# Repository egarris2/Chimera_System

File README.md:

View this project on [CADLAB.io](https://cadlab.io/project/27528). 

# Chimera_System
A modular PCB system designed for rapid iteration and extreme flexibility in application.

All PCBs are designed in KiCAD 7. They utilize components that are available from the easyEDA component library which allows for quick generation of manufacturing files for order of assembly from JLCPCB.

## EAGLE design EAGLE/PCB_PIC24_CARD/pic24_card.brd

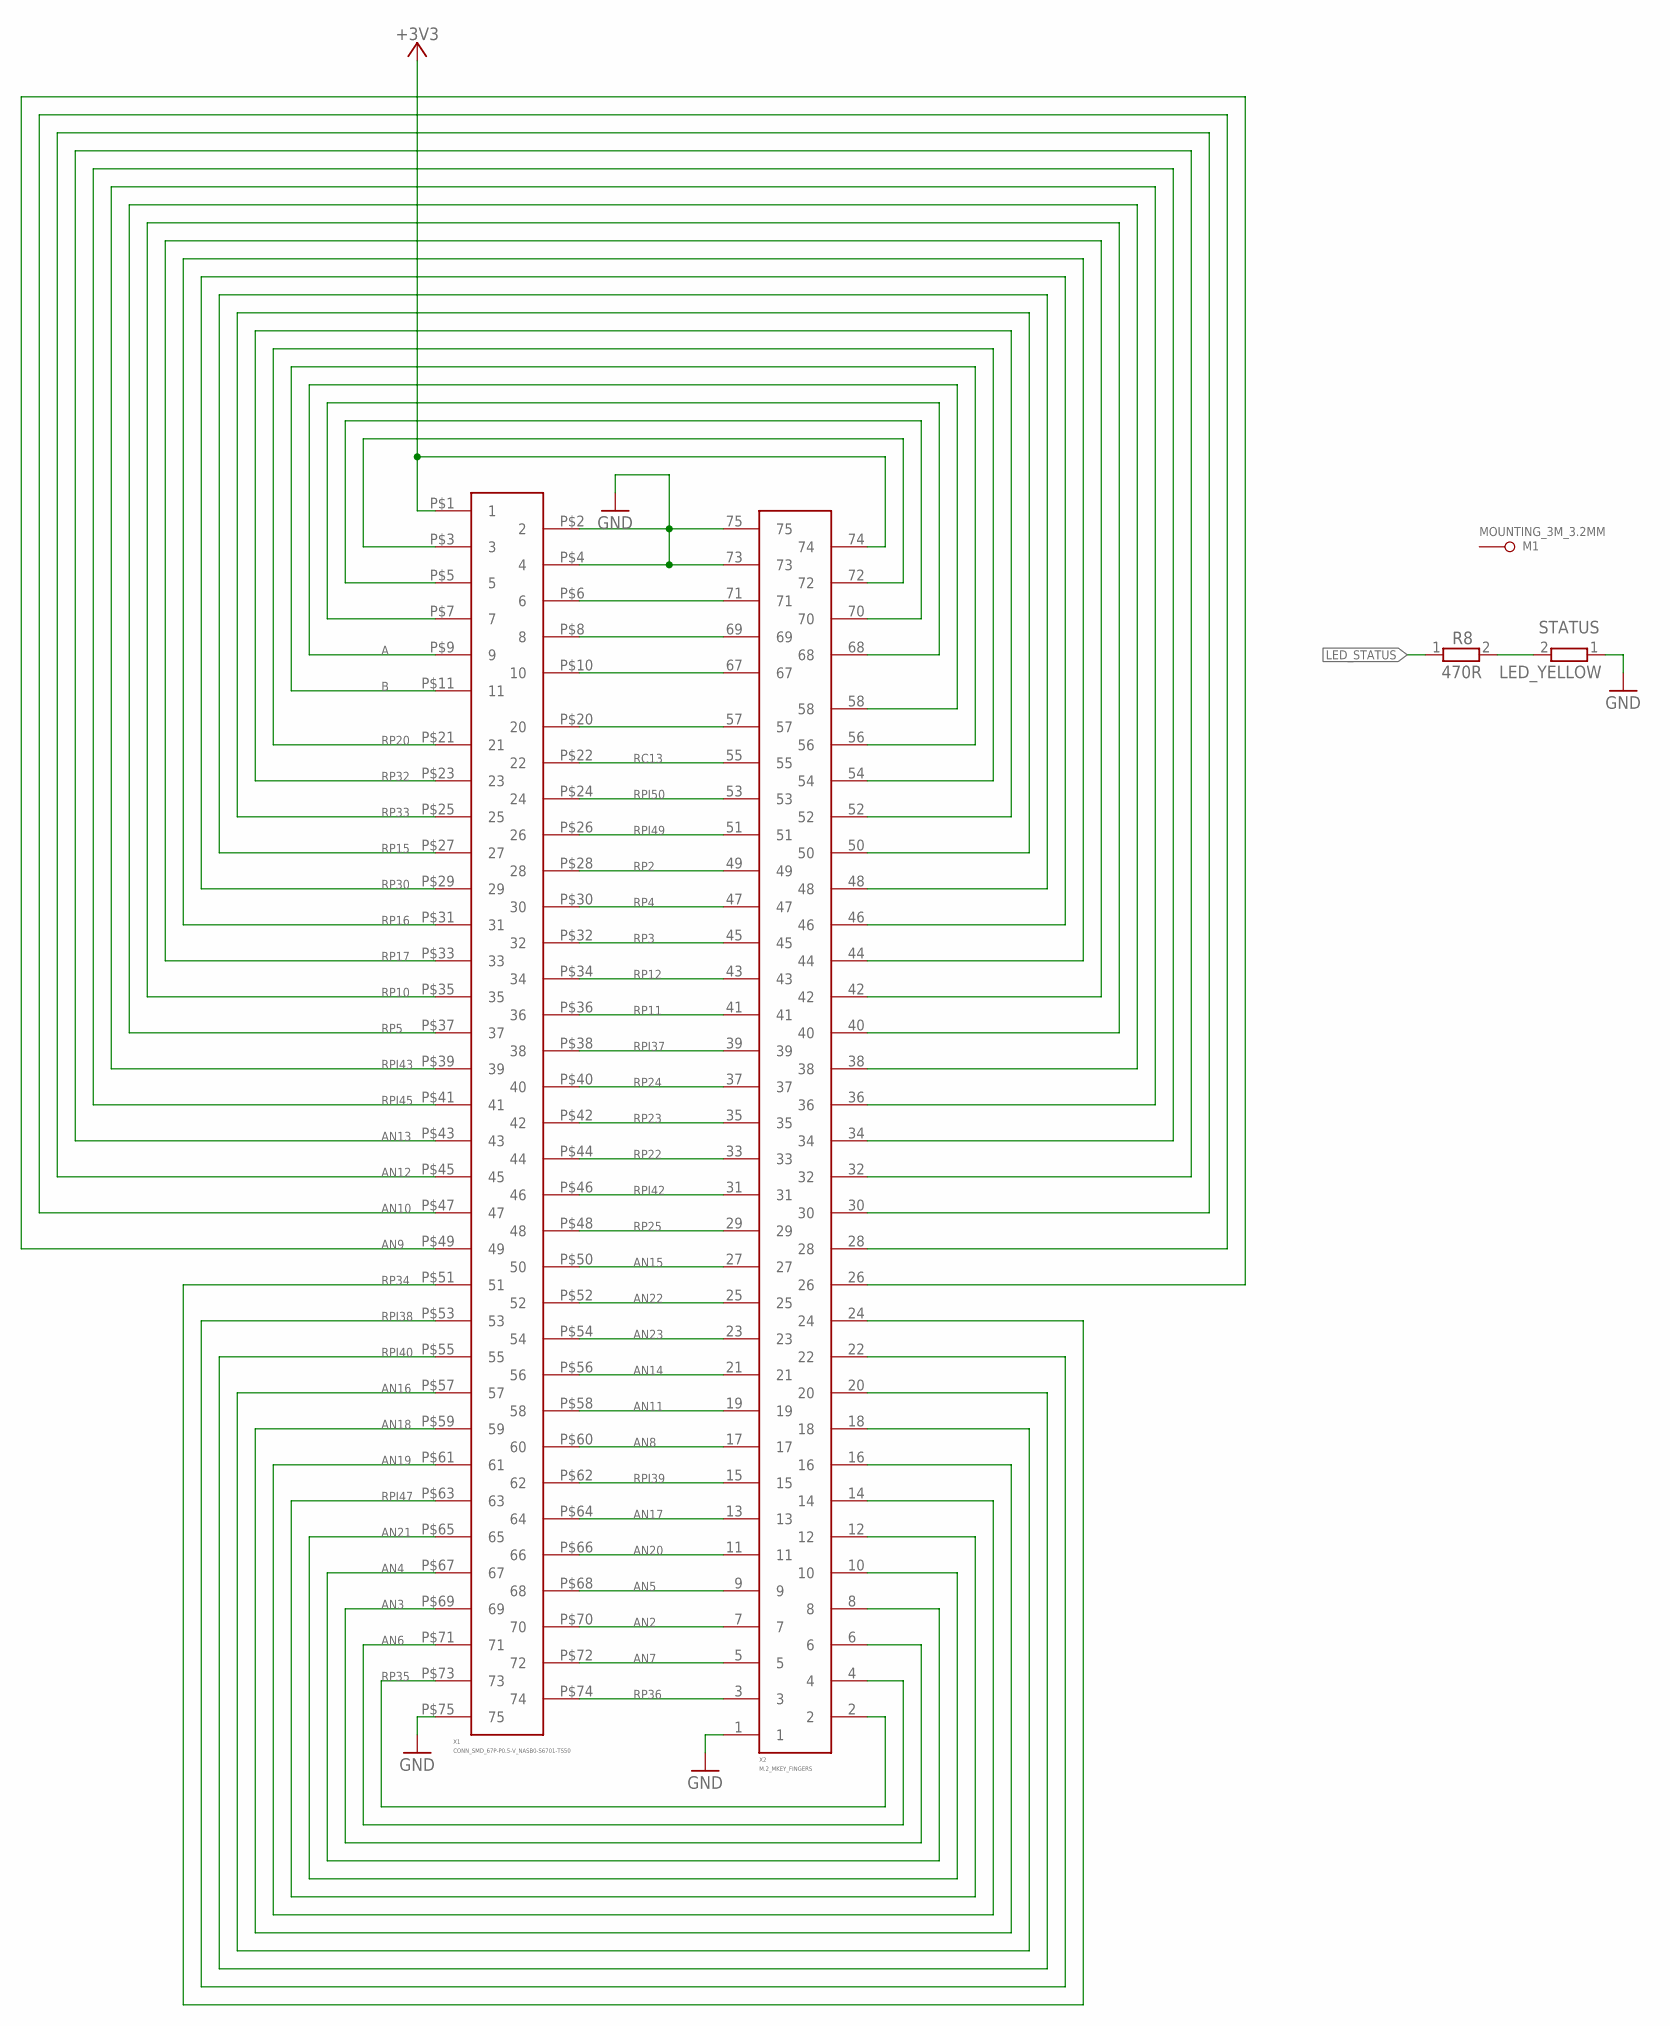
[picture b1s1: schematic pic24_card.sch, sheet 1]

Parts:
M1: MOUNTING_3M_3.2MM
R8: 470R; R0402_NIBE
STATUS: LED_YELLOW; R0603
X1: CONN_SMD_67P-P0.5-V_NASB0-S6701-TS50
X2: M.2_MKEY_FINGERS

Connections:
+3V3: X1.P$1 (1), X2.74; also elsewhere on the board
A: X1.P$9 (9), X2.58; also elsewhere on the board
AN2: X1.P$70 (70), X2.7; also elsewhere on the board
AN3: X1.P$69 (69), X2.6; also elsewhere on the board
AN4: X1.P$67 (67), X2.8; also elsewhere on the board
AN5: X1.P$68 (68), X2.9; also elsewhere on the board
AN6: X1.P$71 (71), X2.4; also elsewhere on the board
AN7: X1.P$72 (72), X2.5; also elsewhere on the board
AN8: X1.P$60 (60), X2.17; also elsewhere on the board
AN9: X1.P$49 (49), X2.26; also elsewhere on the board
AN10: X1.P$47 (47), X2.28; also elsewhere on the board
AN11: X1.P$58 (58), X2.19; also elsewhere on the board
AN12: X1.P$45 (45), X2.30; also elsewhere on the board
AN13: X1.P$43 (43), X2.32; also elsewhere on the board
AN14: X1.P$56 (56), X2.21; also elsewhere on the board
AN15: X1.P$50 (50), X2.27; also elsewhere on the board
AN16: X1.P$57 (57), X2.18; also elsewhere on the board
AN17: X1.P$64 (64), X2.13; also elsewhere on the board
AN18: X1.P$59 (59), X2.16; also elsewhere on the board
AN19: X1.P$61 (61), X2.14; also elsewhere on the board
AN20: X1.P$66 (66), X2.11; also elsewhere on the board
AN21: X1.P$65 (65), X2.10; also elsewhere on the board
AN22: X1.P$52 (52), X2.25; also elsewhere on the board
AN23: X1.P$54 (54), X2.23; also elsewhere on the board
B: X1.P$11 (11), X2.56; also elsewhere on the board
GND: STATUS.1 (2), X1.P$2 (2), X1.P$4 (4), X1.P$75 (75), X2.1, X2.73, X2.75; also elsewhere on the board
LED_STATUS: R8.1; also elsewhere on the board
unnamed: R8.2, STATUS.2 (1)
unnamed: X1.P$7 (7), X2.68
unnamed: X1.P$5 (5), X2.70
unnamed: X1.P$3 (3), X2.72
unnamed: X1.P$6 (6), X2.71
unnamed: X1.P$8 (8), X2.69
unnamed: X1.P$10 (10), X2.67
unnamed: X1.P$20 (20), X2.57
RC13: X1.P$22 (22), X2.55; also elsewhere on the board
RP2: X1.P$28 (28), X2.49; also elsewhere on the board
RP3: X1.P$32 (32), X2.45; also elsewhere on the board
RP4: X1.P$30 (30), X2.47; also elsewhere on the board
RP5: X1.P$37 (37), X2.38; also elsewhere on the board
RP10: X1.P$35 (35), X2.40; also elsewhere on the board
RP11: X1.P$36 (36), X2.41; also elsewhere on the board
RP12: X1.P$34 (34), X2.43; also elsewhere on the board
RP15: X1.P$27 (27), X2.48; also elsewhere on the board
RP16: X1.P$31 (31), X2.44; also elsewhere on the board
RP17: X1.P$33 (33), X2.42; also elsewhere on the board
RP20: X1.P$21 (21), X2.54; also elsewhere on the board
RP22: X1.P$44 (44), X2.33; also elsewhere on the board
RP23: X1.P$42 (42), X2.35; also elsewhere on the board
RP24: X1.P$40 (40), X2.37; also elsewhere on the board
RP25: X1.P$48 (48), X2.29; also elsewhere on the board
RP30: X1.P$29 (29), X2.46; also elsewhere on the board
RP32: X1.P$23 (23), X2.52; also elsewhere on the board
RP33: X1.P$25 (25), X2.50; also elsewhere on the board
RP34: X1.P$51 (51), X2.24; also elsewhere on the board
RP35: X1.P$73 (73), X2.2; also elsewhere on the board
RP36: X1.P$74 (74), X2.3; also elsewhere on the board
RPI37: X1.P$38 (38), X2.39; also elsewhere on the board
RPI38: X1.P$53 (53), X2.22; also elsewhere on the board
RPI39: X1.P$62 (62), X2.15; also elsewhere on the board
RPI40: X1.P$55 (55), X2.20; also elsewhere on the board
RPI42: X1.P$46 (46), X2.31; also elsewhere on the board
RPI43: X1.P$39 (39), X2.36; also elsewhere on the board
RPI45: X1.P$41 (41), X2.34; also elsewhere on the board
RPI47: X1.P$63 (63), X2.12; also elsewhere on the board
RPI49: X1.P$26 (26), X2.51; also elsewhere on the board
RPI50: X1.P$24 (24), X2.53; also elsewhere on the board

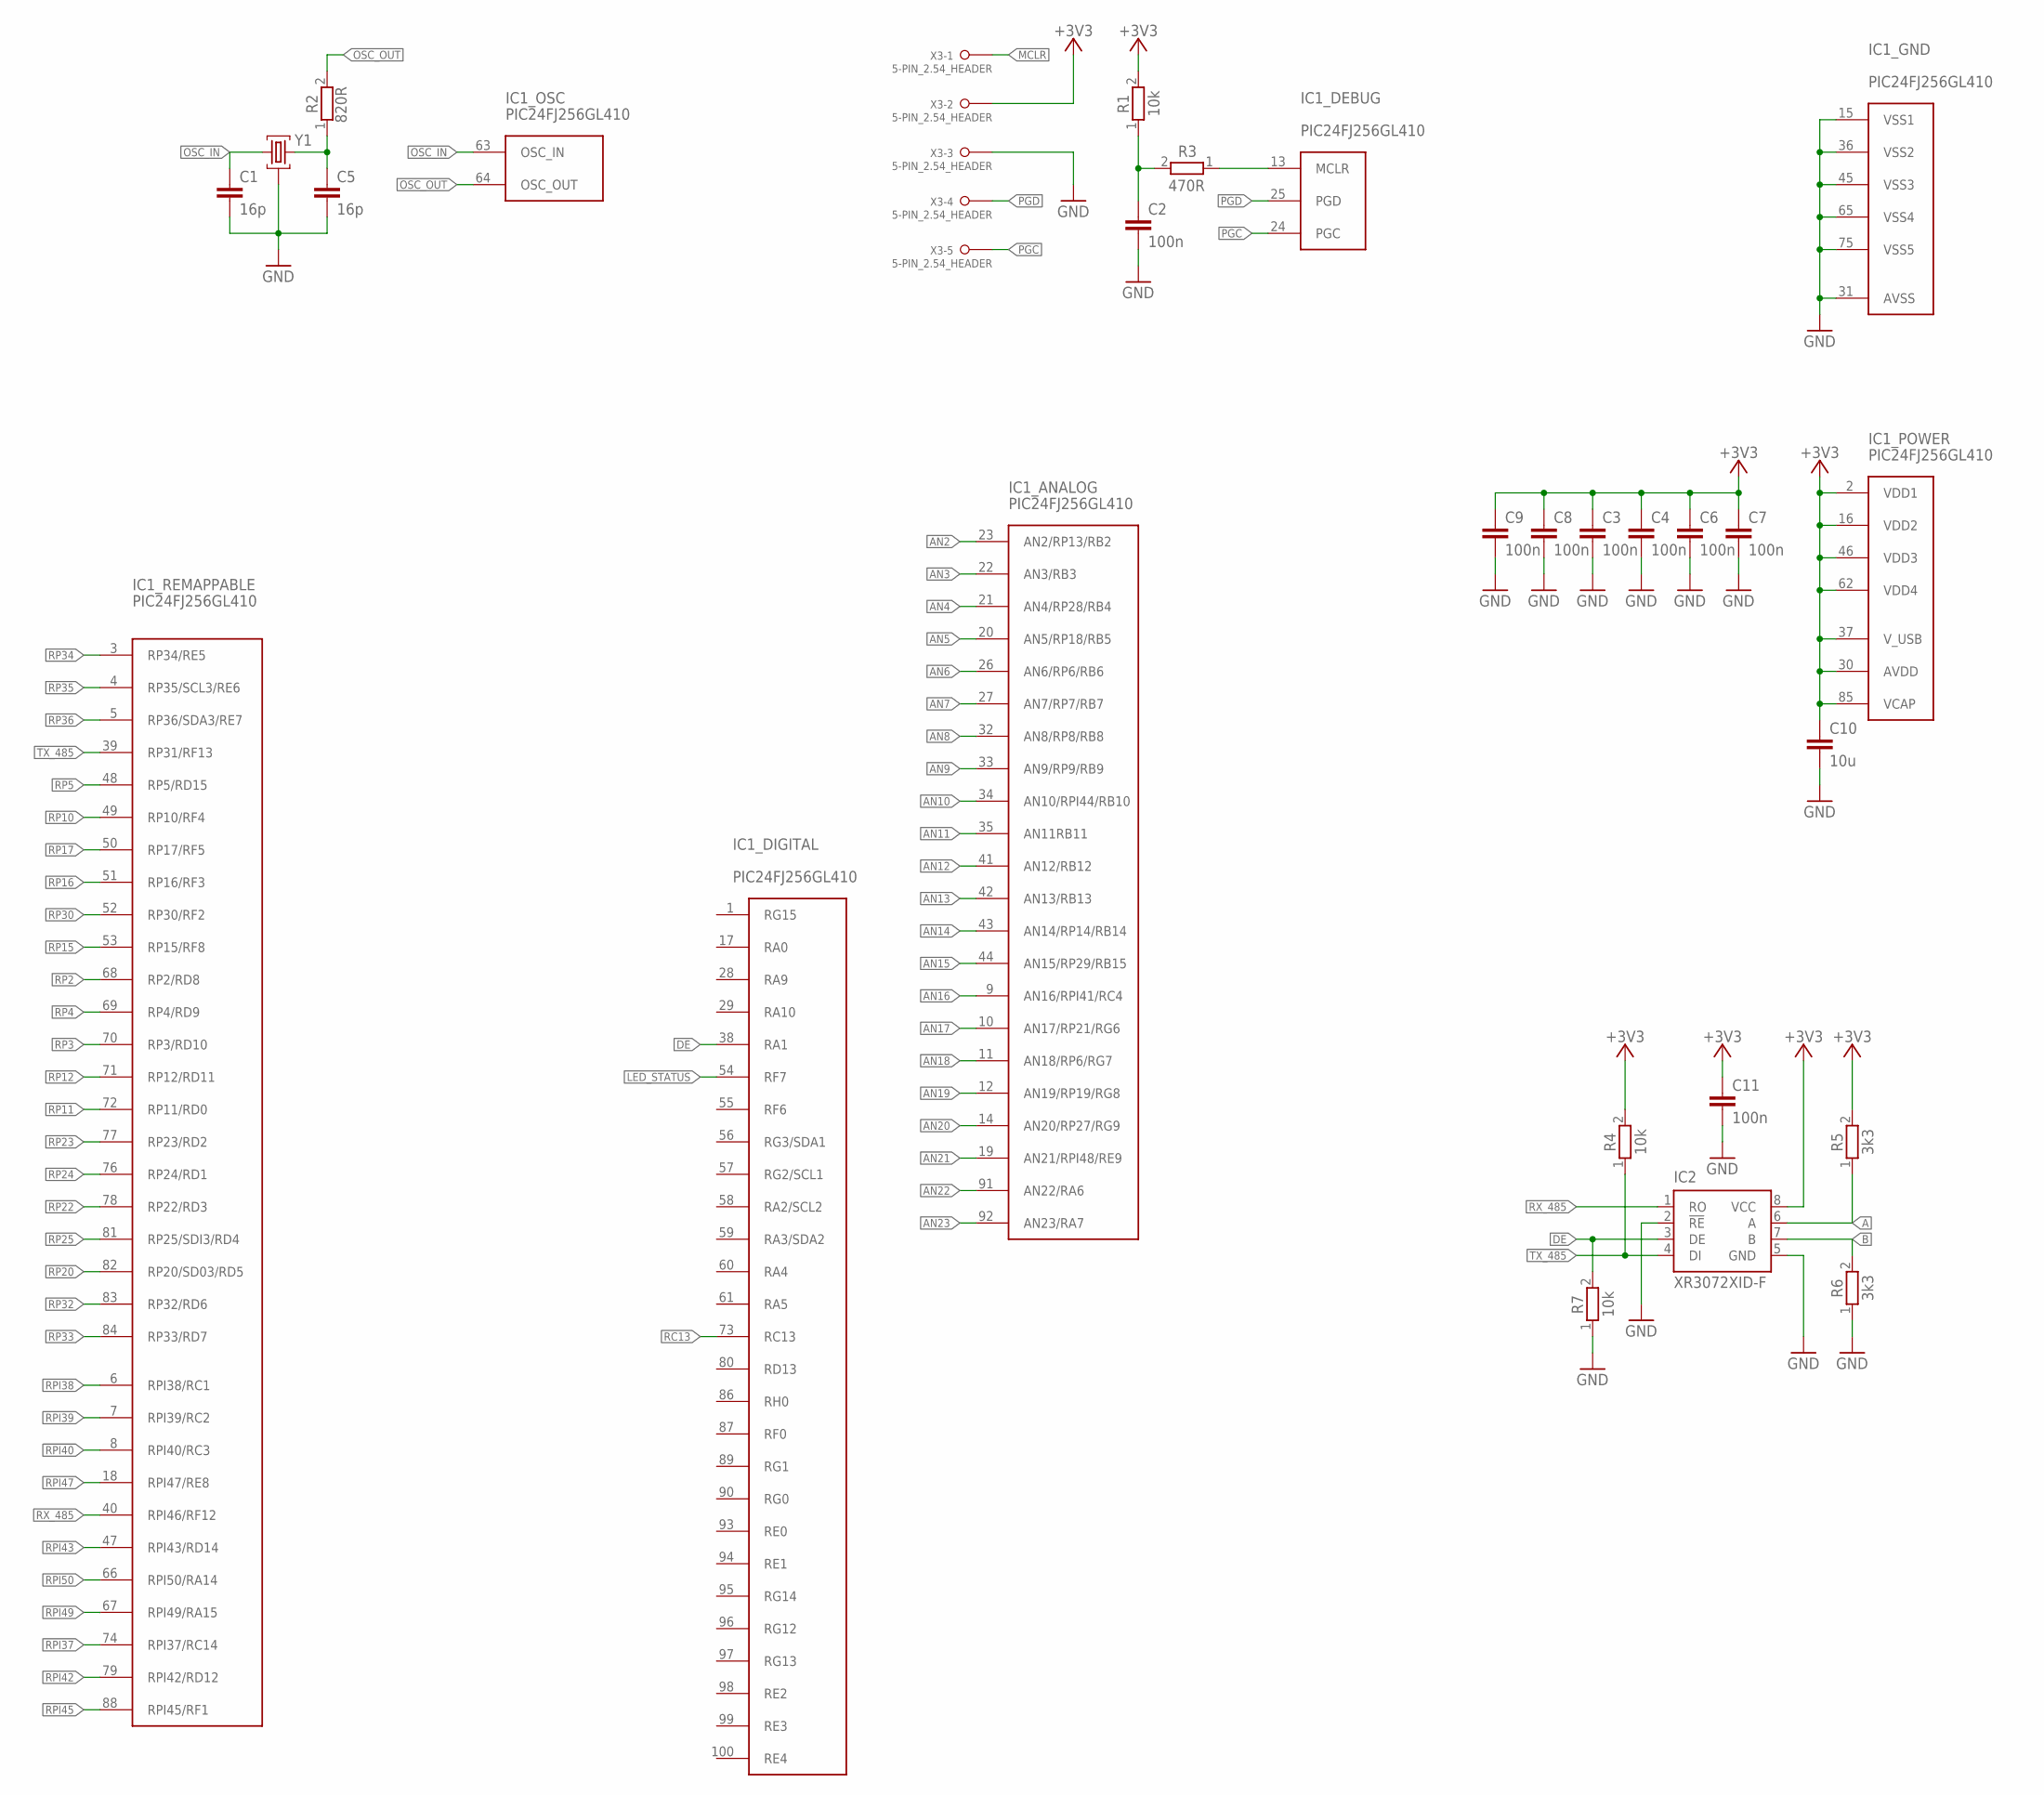
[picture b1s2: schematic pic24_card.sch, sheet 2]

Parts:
C1, C5: 16p; C0402_NIBE
C2, C3, C4, C6, C7, C8, C9, C11: 100n; C0402_NIBE
C10: 10u; C0805
IC1: PIC24FJ256GL410
IC2: XR3072XID-F; SOIC8
R1, R4, R7: 10k; R0402_NIBE
R2: 820R; R0402_NIBE
R3: 470R; R0402_NIBE
R5, R6: 3k3; R0402_NIBE
X3: 5-PIN_2.54_HEADER; 2.54MM_5HOLE_TH
Y1: FA238-12MHZ; FA238

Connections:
+3V3: C3.1, C4.1, C6.1, C7.1, C8.1, C9.1, C10.1, C11.1, IC1.2 (VDD1), IC1.16 (VDD2), IC1.30 (AVDD), IC1.37 (V_USB), IC1.46 (VDD3), IC1.62 (VDD4), IC1.85 (VCAP), IC2.8 (VCC), R1.2, R4.2, R5.2, X3.2; also elsewhere on the board
A: IC2.6 (A), R5.1; also elsewhere on the board
AN2: IC1.23 (AN2/RP13/RB2); also elsewhere on the board
AN3: IC1.22 (AN3/RB3); also elsewhere on the board
AN4: IC1.21 (AN4/RP28/RB4); also elsewhere on the board
AN5: IC1.20 (AN5/RP18/RB5); also elsewhere on the board
AN6: IC1.26 (AN6/RP6/RB6); also elsewhere on the board
AN7: IC1.27 (AN7/RP7/RB7); also elsewhere on the board
AN8: IC1.32 (AN8/RP8/RB8); also elsewhere on the board
AN9: IC1.33 (AN9/RP9/RB9); also elsewhere on the board
AN10: IC1.34 (AN10/RPI44/RB10); also elsewhere on the board
AN11: IC1.35 (AN11RB11); also elsewhere on the board
AN12: IC1.41 (AN12/RB12); also elsewhere on the board
AN13: IC1.42 (AN13/RB13); also elsewhere on the board
AN14: IC1.43 (AN14/RP14/RB14); also elsewhere on the board
AN15: IC1.44 (AN15/RP29/RB15); also elsewhere on the board
AN16: IC1.9 (AN16/RPI41/RC4); also elsewhere on the board
AN17: IC1.10 (AN17/RP21/RG6); also elsewhere on the board
AN18: IC1.11 (AN18/RP6/RG7); also elsewhere on the board
AN19: IC1.12 (AN19/RP19/RG8); also elsewhere on the board
AN20: IC1.14 (AN20/RP27/RG9); also elsewhere on the board
AN21: IC1.19 (AN21/RPI48/RE9); also elsewhere on the board
AN22: IC1.91 (AN22/RA6); also elsewhere on the board
AN23: IC1.92 (AN23/RA7); also elsewhere on the board
B: IC2.7 (B), R6.2; also elsewhere on the board
DE: IC1.38 (RA1), IC2.3 (DE), R7.2
GND: C1.2, C2.2, C3.2, C4.2, C5.2, C6.2, C7.2, C8.2, C9.2, C10.2, C11.2, IC1.15 (VSS1), IC1.31 (AVSS), IC1.36 (VSS2), IC1.45 (VSS3), IC1.65 (VSS4), IC1.75 (VSS5), IC2.2 (!RE), IC2.5 (GND), R6.1, R7.1, X3.3, Y1.2, Y1.4 (2); also elsewhere on the board
LED_STATUS: IC1.54 (RF7); also elsewhere on the board
MCLR: IC1.13 (MCLR), R3.1, X3.1
unnamed: C2.1, R1.1, R3.2
unnamed: C5.1, R2.1, Y1.3
OSC_IN: C1.1, IC1.63 (OSC_IN), Y1.1
OSC_OUT: IC1.64 (OSC_OUT), R2.2
PGC: IC1.24 (PGC), X3.5
PGD: IC1.25 (PGD), X3.4
RC13: IC1.73 (RC13); also elsewhere on the board
RP2: IC1.68 (RP2/RD8); also elsewhere on the board
RP3: IC1.70 (RP3/RD10); also elsewhere on the board
RP4: IC1.69 (RP4/RD9); also elsewhere on the board
RP5: IC1.48 (RP5/RD15); also elsewhere on the board
RP10: IC1.49 (RP10/RF4); also elsewhere on the board
RP11: IC1.72 (RP11/RD0); also elsewhere on the board
RP12: IC1.71 (RP12/RD11); also elsewhere on the board
RP15: IC1.53 (RP15/RF8); also elsewhere on the board
RP16: IC1.51 (RP16/RF3); also elsewhere on the board
RP17: IC1.50 (RP17/RF5); also elsewhere on the board
RP20: IC1.82 (RP20/SD03/RD5); also elsewhere on the board
RP22: IC1.78 (RP22/RD3); also elsewhere on the board
RP23: IC1.77 (RP23/RD2); also elsewhere on the board
RP24: IC1.76 (RP24/RD1); also elsewhere on the board
RP25: IC1.81 (RP25/SDI3/RD4); also elsewhere on the board
RP30: IC1.52 (RP30/RF2); also elsewhere on the board
RP32: IC1.83 (RP32/RD6); also elsewhere on the board
RP33: IC1.84 (RP33/RD7); also elsewhere on the board
RP34: IC1.3 (RP34/RE5); also elsewhere on the board
RP35: IC1.4 (RP35/SCL3/RE6); also elsewhere on the board
RP36: IC1.5 (RP36/SDA3/RE7); also elsewhere on the board
RPI37: IC1.74 (RPI37/RC14); also elsewhere on the board
RPI38: IC1.6 (RPI38/RC1); also elsewhere on the board
RPI39: IC1.7 (RPI39/RC2); also elsewhere on the board
RPI40: IC1.8 (RPI40/RC3); also elsewhere on the board
RPI42: IC1.79 (RPI42/RD12); also elsewhere on the board
RPI43: IC1.47 (RPI43/RD14); also elsewhere on the board
RPI45: IC1.88 (RPI45/RF1); also elsewhere on the board
RPI47: IC1.18 (RPI47/RE8); also elsewhere on the board
RPI49: IC1.67 (RPI49/RA15); also elsewhere on the board
RPI50: IC1.66 (RPI50/RA14); also elsewhere on the board
RX_485: IC1.40 (RPI46/RF12), IC2.1 (RO)
TX_485: IC1.39 (RP31/RF13), IC2.4 (DI), R4.1

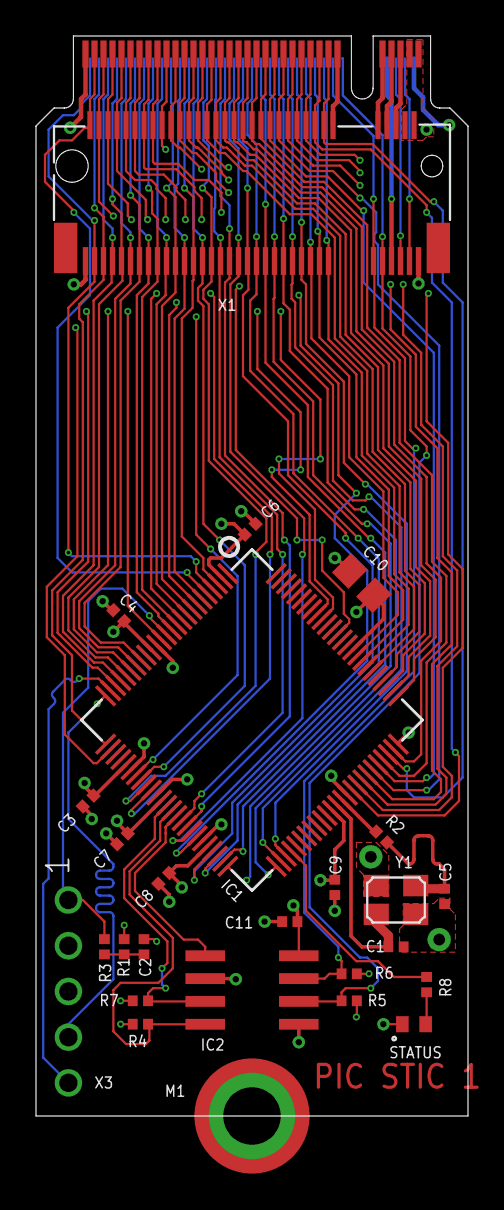
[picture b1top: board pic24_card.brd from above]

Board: 4 copper layers, 24.0 x 60.0 mm, 27 parts (0 on the bottom side), 77 nets.

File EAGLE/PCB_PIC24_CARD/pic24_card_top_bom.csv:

Comment,Designator,Footprint,LCSC Part #
12MHz,Y1,FA238,
3k3,R5 R6,R0402_NIBE,C3969551
10k,R1 R4 R7,R0402_NIBE,C2838653
10u,C10,C0805,C882505
16p,C1 C5,C0402_NIBE,C161307
100n,C2 C3 C4 C6 C7 C8 C9 C11,C0402_NIBE,C327273
470R,R3 R8,R0402_NIBE,C606172
820R,R2,R0402_NIBE,C227421
CONN_SMD_67P-P0.5-V_NASB0-S6701-TS50,X1,CONN_SMD_67P-P0.5-V_NASB0-S6701-TS50,C367024
LED_YELLOW,STATUS,R0603,C511086
M.2_MKEY_FINGERS,X2,M.2_MKEY_FINGERS,
MOUNTING_3M_3.2MM,M1,MOUNTING_3M_3.2MM,
PIC24FJ256GL410,IC1,PIC24FJ256GL410,C1015827
XR3072XID-F,IC2,SOIC8,

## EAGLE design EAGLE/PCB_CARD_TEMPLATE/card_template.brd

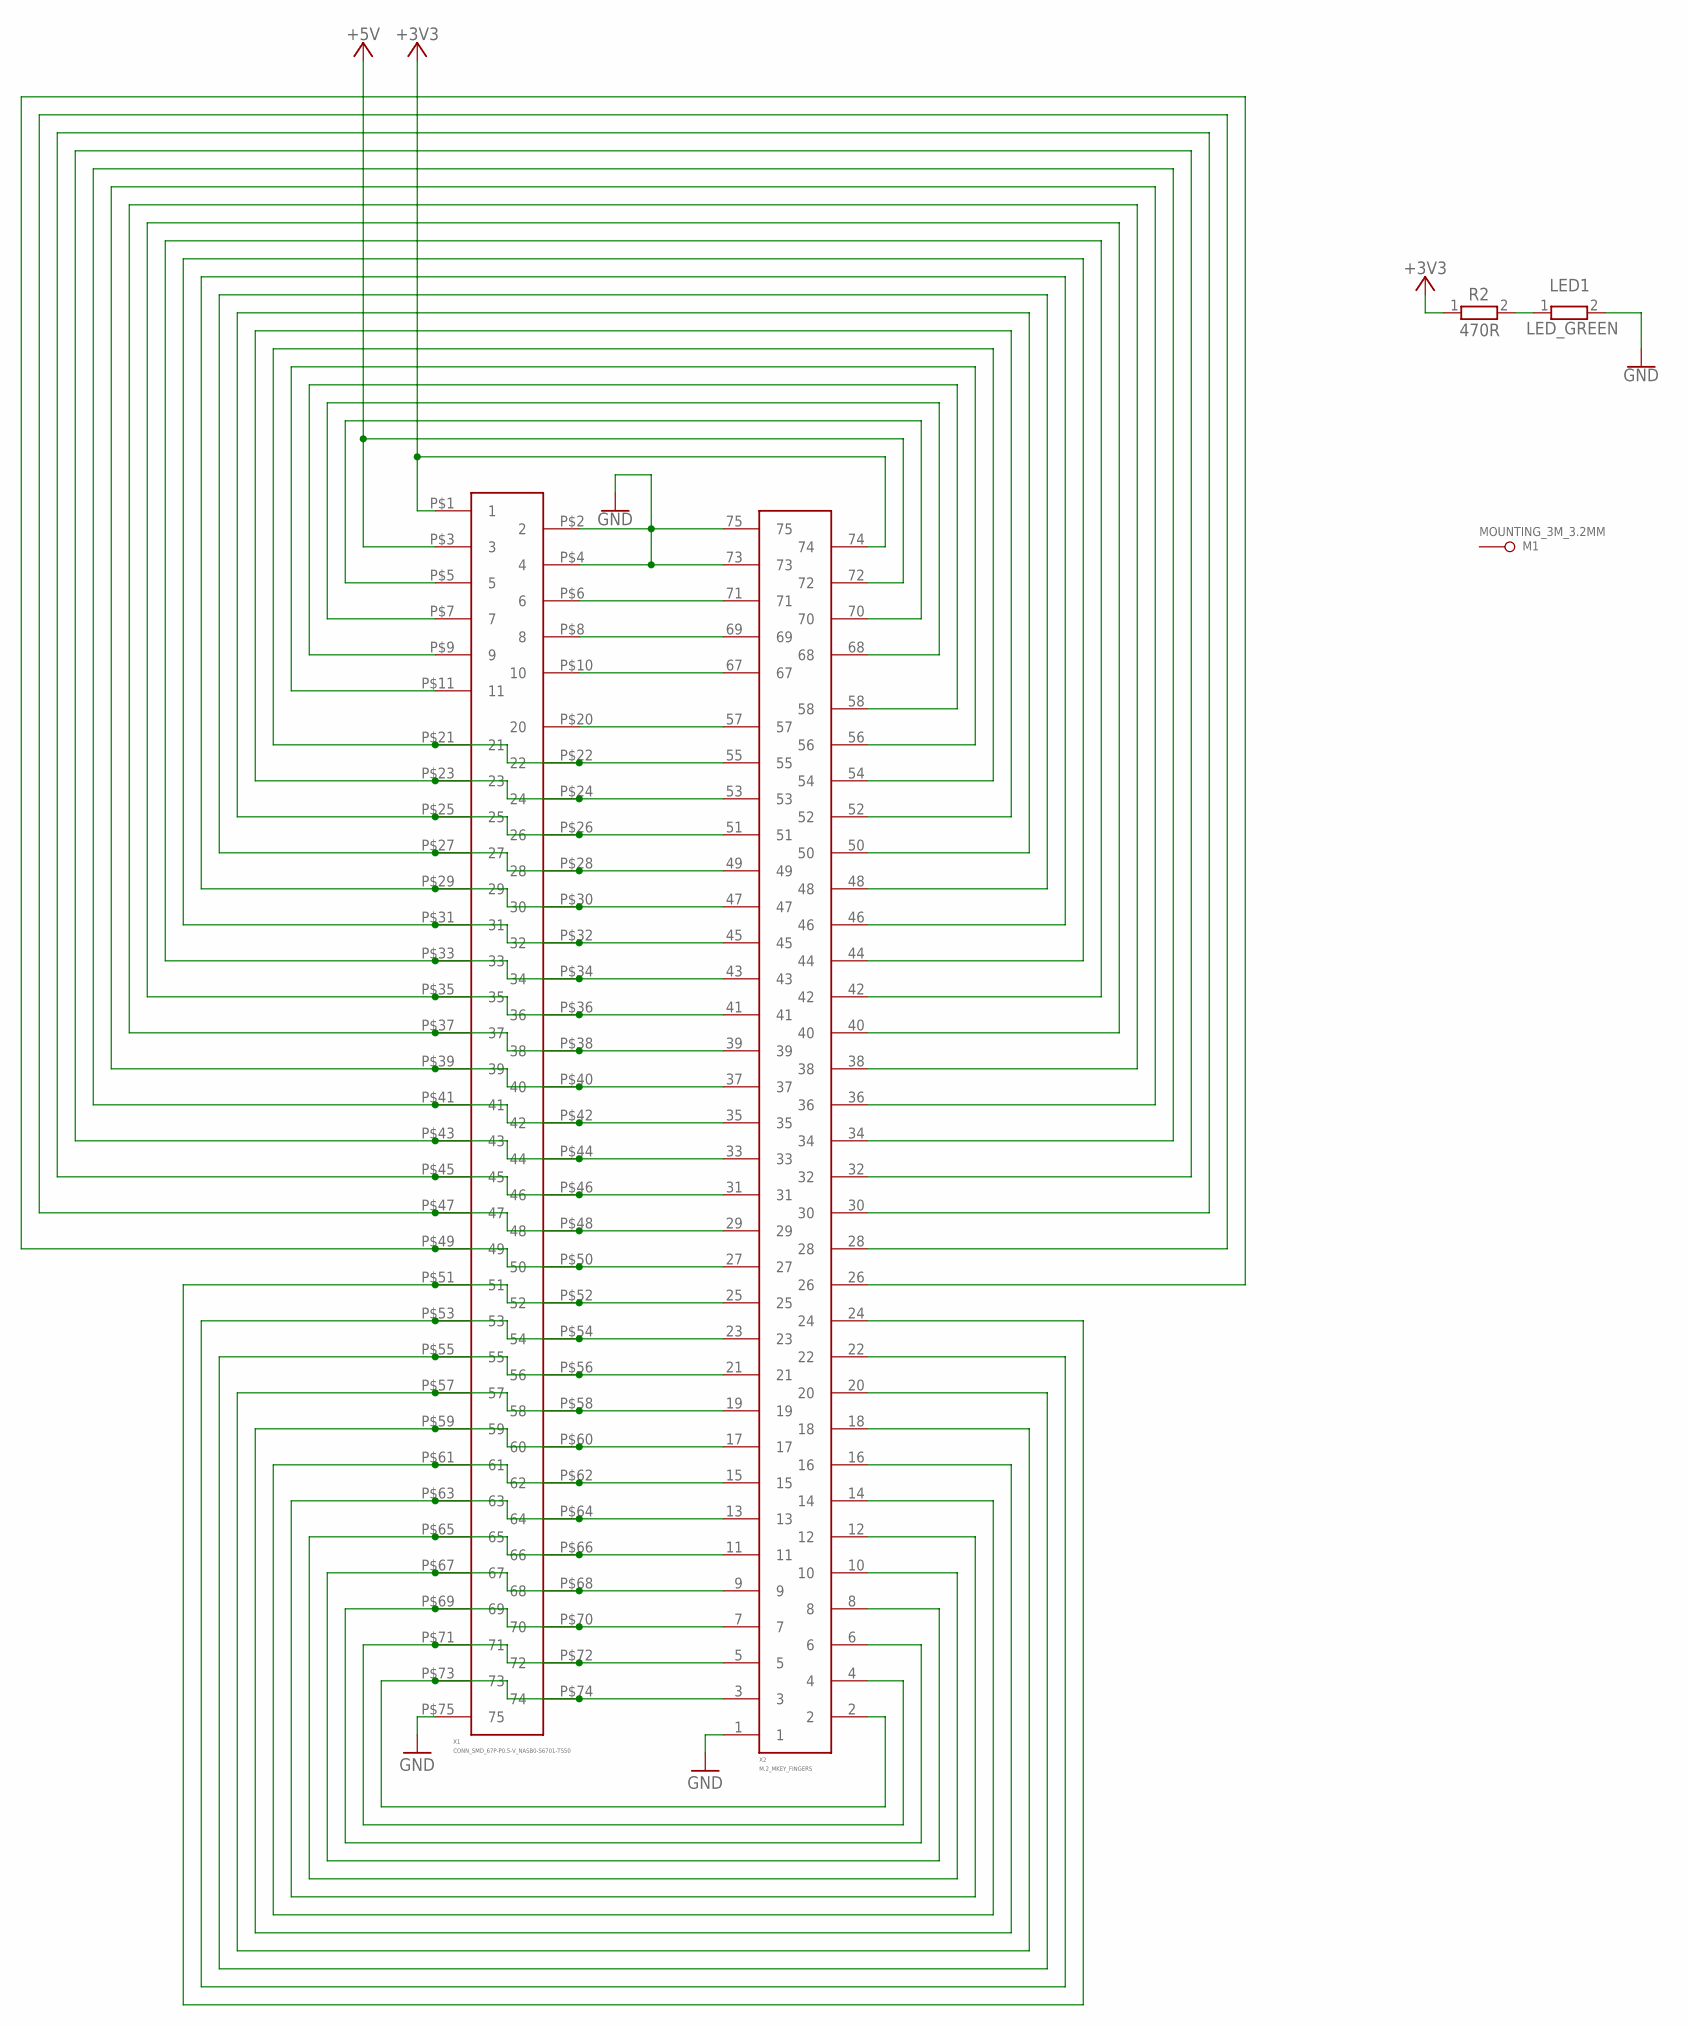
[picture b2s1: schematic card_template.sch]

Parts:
LED1: LED_GREEN; R0603
M1: MOUNTING_3M_3.2MM
R2: 470R; R0603
X1: CONN_SMD_67P-P0.5-V_NASB0-S6701-TS50
X2: M.2_MKEY_FINGERS

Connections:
+3V3: R2.1, X1.P$1 (1), X2.74
+5V: X1.P$3 (3), X2.72
GND: LED1.2, X1.P$2 (2), X1.P$4 (4), X1.P$75 (75), X2.1, X2.73, X2.75
unnamed: X1.P$23 (23), X1.P$24 (24), X2.52, X2.53
unnamed: X1.P$25 (25), X1.P$26 (26), X2.50, X2.51
unnamed: X1.P$73 (73), X1.P$74 (74), X2.2, X2.3
unnamed: X1.P$71 (71), X1.P$72 (72), X2.4, X2.5
unnamed: X1.P$69 (69), X1.P$70 (70), X2.6, X2.7
unnamed: X1.P$67 (67), X1.P$68 (68), X2.8, X2.9
unnamed: X1.P$65 (65), X1.P$66 (66), X2.10, X2.11
unnamed: X1.P$63 (63), X1.P$64 (64), X2.12, X2.13
unnamed: X1.P$61 (61), X1.P$62 (62), X2.14, X2.15
unnamed: X1.P$59 (59), X1.P$60 (60), X2.16, X2.17
unnamed: X1.P$57 (57), X1.P$58 (58), X2.18, X2.19
unnamed: X1.P$55 (55), X1.P$56 (56), X2.20, X2.21
unnamed: X1.P$53 (53), X1.P$54 (54), X2.22, X2.23
unnamed: X1.P$51 (51), X1.P$52 (52), X2.24, X2.25
unnamed: X1.P$21 (21), X1.P$22 (22), X2.54, X2.55
unnamed: X1.P$27 (27), X1.P$28 (28), X2.48, X2.49
unnamed: X1.P$29 (29), X1.P$30 (30), X2.46, X2.47
unnamed: X1.P$31 (31), X1.P$32 (32), X2.44, X2.45
unnamed: X1.P$33 (33), X1.P$34 (34), X2.42, X2.43
unnamed: X1.P$35 (35), X1.P$36 (36), X2.40, X2.41
unnamed: X1.P$37 (37), X1.P$38 (38), X2.38, X2.39
unnamed: X1.P$39 (39), X1.P$40 (40), X2.36, X2.37
unnamed: X1.P$41 (41), X1.P$42 (42), X2.34, X2.35
unnamed: X1.P$43 (43), X1.P$44 (44), X2.32, X2.33
unnamed: X1.P$45 (45), X1.P$46 (46), X2.30, X2.31
unnamed: X1.P$47 (47), X1.P$48 (48), X2.28, X2.29
unnamed: X1.P$49 (49), X1.P$50 (50), X2.26, X2.27
unnamed: X1.P$11 (11), X2.56
unnamed: X1.P$9 (9), X2.58
unnamed: X1.P$7 (7), X2.68
unnamed: X1.P$5 (5), X2.70
unnamed: LED1.1, R2.2
unnamed: X1.P$6 (6), X2.71
unnamed: X1.P$8 (8), X2.69
unnamed: X1.P$10 (10), X2.67
unnamed: X1.P$20 (20), X2.57

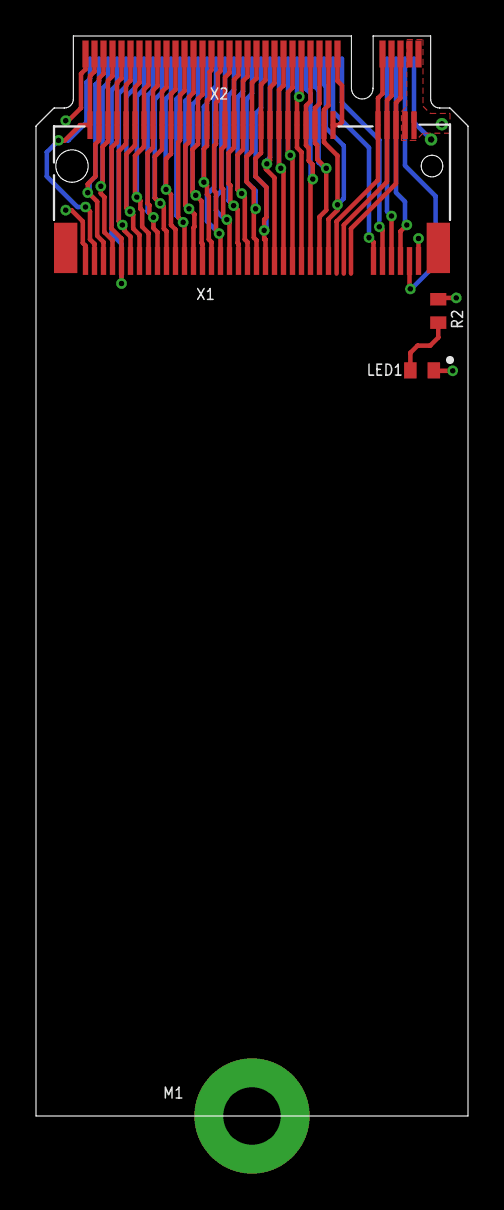
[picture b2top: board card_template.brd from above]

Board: 4 copper layers, 24.0 x 60.0 mm, 5 parts (0 on the bottom side), 39 nets.
